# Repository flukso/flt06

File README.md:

# flt06
PCB for testing the Fluksometer

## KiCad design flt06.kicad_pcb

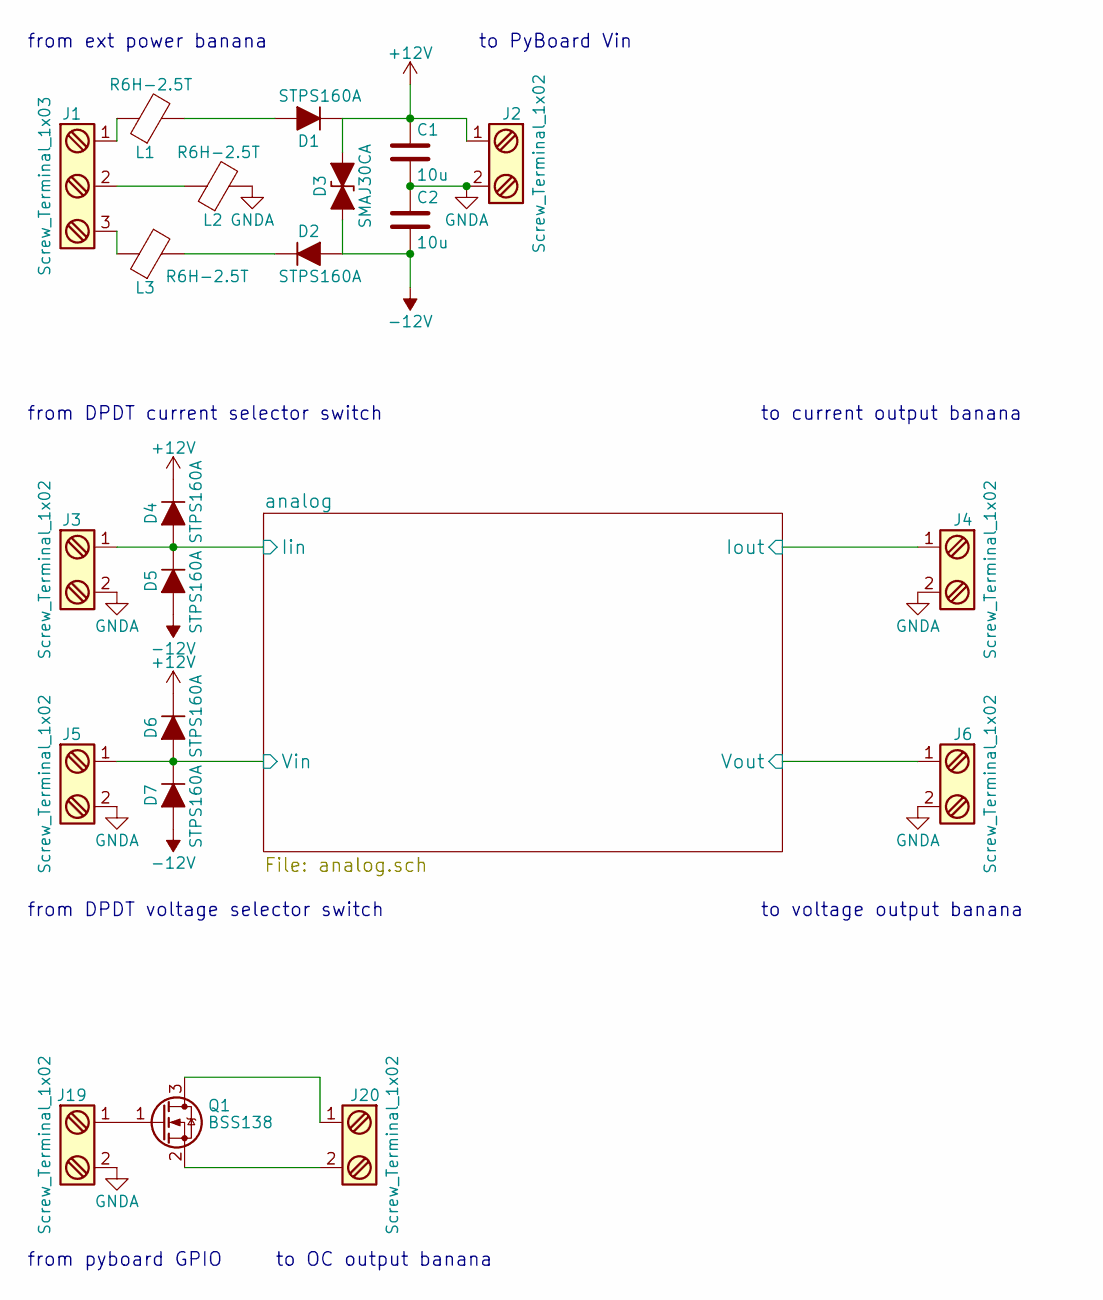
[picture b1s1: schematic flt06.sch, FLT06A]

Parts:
C1, C2: 10u; C_1210
D1, D2, D4, D5, D6, D7: STPS160A; D_SMA
D3: SMAJ30CA; D_SMA
J1: Screw_Terminal_1x03; TerminalBlock_Pheonix_PT-3.5mm_3pol
J2, J3, J4, J5, J6, J19, J20: Screw_Terminal_1x02; TerminalBlock_Pheonix_PT-3.5mm_2pol
L1, L2, L3: R6H-2.5T; R_Axial_DIN0617_L17.0mm_D6.0mm_P5.08mm_Vertical
Q1: BSS138; SOT-23

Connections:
+12V: C1.1, D1.1 (K), D3.2 (A2), D4.1 (K), D6.1 (K), J2.1; also elsewhere on the board
-12V: C2.2, D2.2 (A), D3.1 (A1), D5.2 (A), D7.2 (A); also elsewhere on the board
/analog/Iin: D4.2 (A), D5.1 (K), J3.1; also elsewhere on the board
/analog/Iout: J4.1; also elsewhere on the board
/analog/Vin: D6.2 (A), D7.1 (K), J5.1; also elsewhere on the board
/analog/Vout: J6.1; also elsewhere on the board
GNDA: C1.2, C2.1, J2.2, J3.2, J4.2, J5.2, J6.2, J19.2, L2.2; also elsewhere on the board
unnamed: D1.2 (A), L1.2
unnamed: D2.1 (K), L3.2
unnamed: J1.1, L1.1
unnamed: J1.2, L2.1
unnamed: J1.3, L3.1
unnamed: J19.1, Q1.1 (G)
unnamed: J20.1, Q1.3 (D)
unnamed: J20.2, Q1.2 (S)

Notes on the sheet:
to PyBoard Vin
from ext power banana
from DPDT current selector switch
from DPDT voltage selector switch
to current output banana
to voltage output banana
from pyboard GPIO
to OC output banana

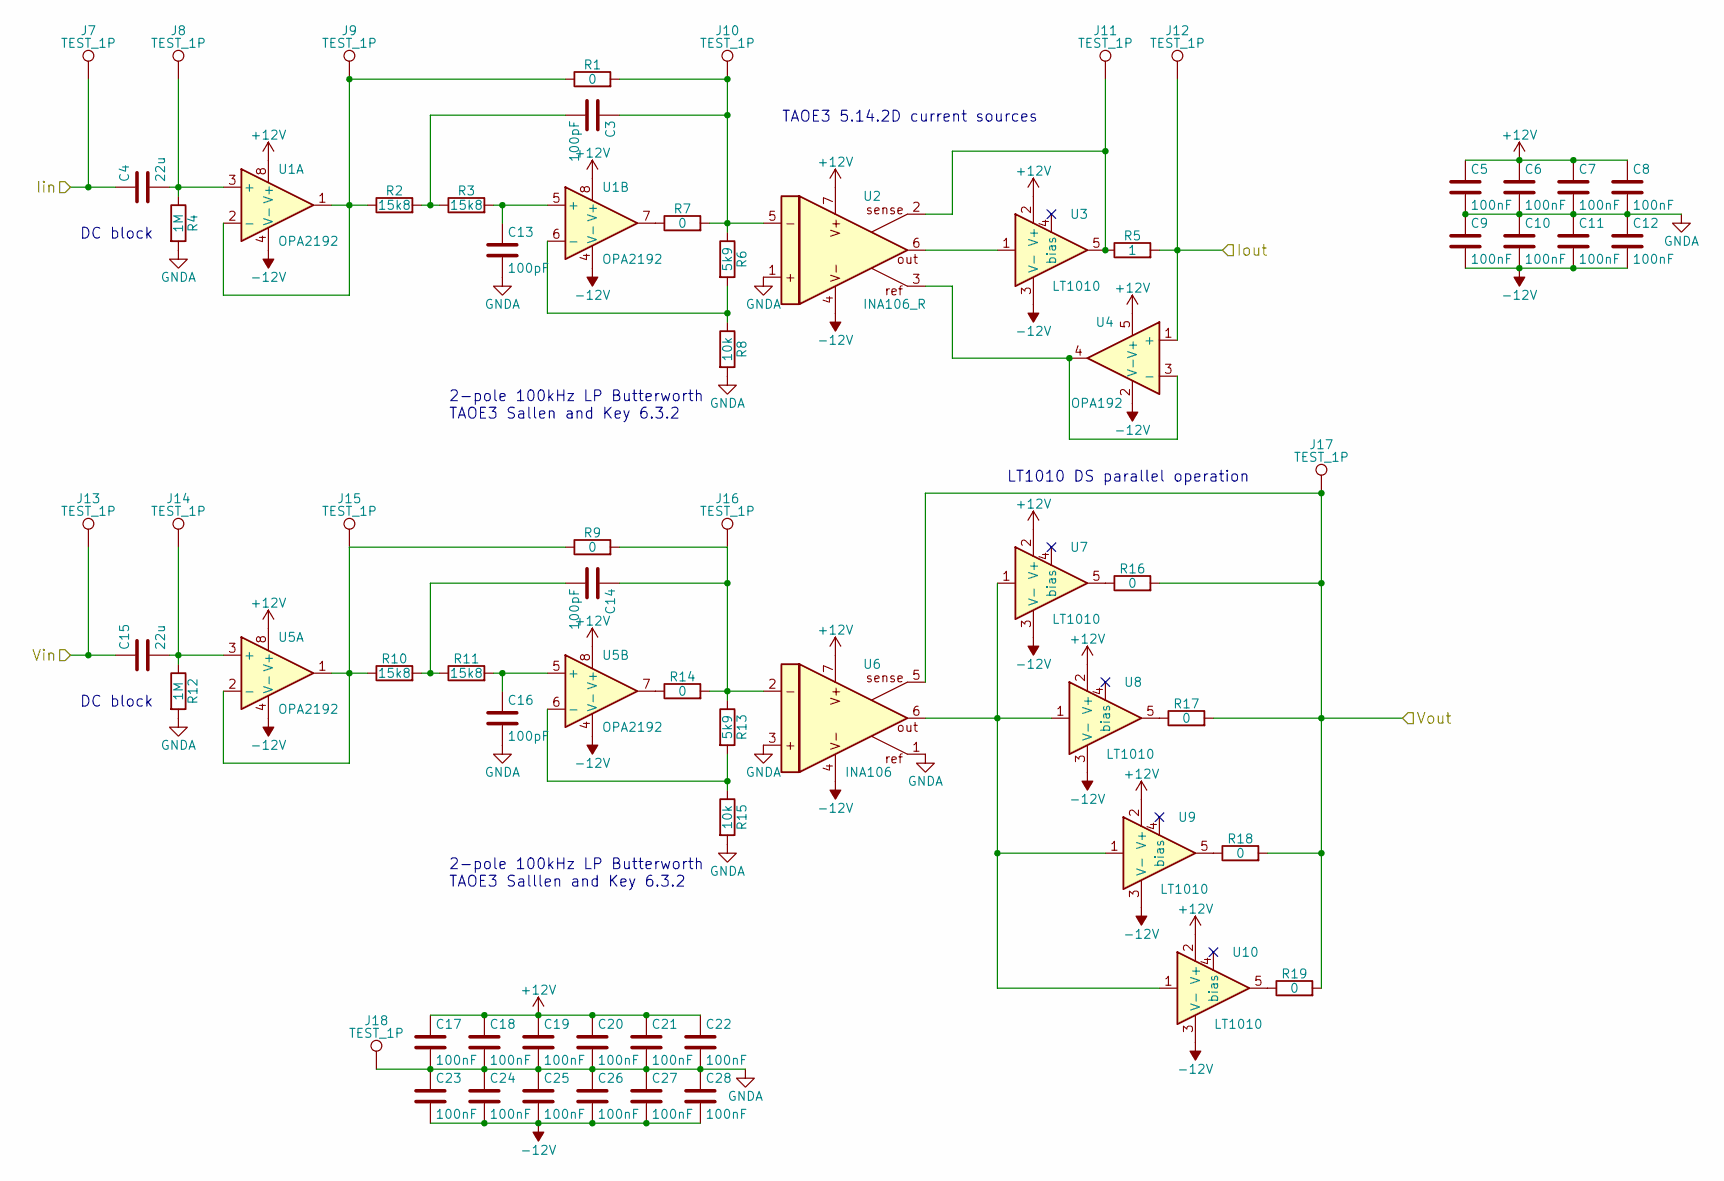
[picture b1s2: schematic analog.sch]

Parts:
C3, C13, C14, C16: 100pF; C_0603
C4, C15: 22u; C_1210
C5, C6, C7, C8, C9, C10, C11, C12, C17, C18, C19, C20, C21, C22, C23, C24, C25, C26, C27, C28: 100nF; C_0603
J7, J8, J9, J10, J11, J12, J13, J14, J15, J16, J17, J18: TEST_1P; Pin_Header_Straight_1x01_Pitch2.54mm
R1, R7, R9, R14: 0; R_0603
R2, R3, R10, R11: 15k8; R_0603
R4, R12: 1M; R_0603
R5: 1; R_1206
R6, R13: 5k9; R_0603
R8, R15: 10k; R_0603
R16, R17, R18, R19: 0; R_1206
U1, U5: OPA2192; TSSOP-8_3x3mm_Pitch0.65mm
U2: INA106_R; SOIC-8_3.9x4.9mm_Pitch1.27mm
U3, U7, U8, U9, U10: LT1010; TO-220-5_Pentawatt_Multiwatt-5_Vertical_StaggeredType1
U4: OPA192; SOT-23-5
U6: INA106; SOIC-8_3.9x4.9mm_Pitch1.27mm

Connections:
+12V: C5.1, C6.1, C7.1, C8.1, C17.1, C18.1, C19.1, C20.1, C21.1, C22.1, U1.8 (V+), U2.7, U3.2 (V+), U4.5 (V+), U5.8 (V+), U6.7, U7.2 (V+), U8.2 (V+), U9.2 (V+), U10.2 (V+); also elsewhere on the board
-12V: C9.2, C10.2, C11.2, C12.2, C23.2, C24.2, C25.2, C26.2, C27.2, C28.2, U1.4 (V-), U2.4, U3.3 (V-), U4.2 (V-), U5.4 (V-), U6.4, U7.3 (V-), U8.3 (V-), U9.3 (V-), U10.3 (V-); also elsewhere on the board
/analog/Iin: C4.1, J7.1; also elsewhere on the board
/analog/Iout: J12.1, R5.2, U4.1 (+); also elsewhere on the board
/analog/Vin: C15.1, J13.1; also elsewhere on the board
/analog/Vout: J17.1, R16.2, R17.2, R18.2, R19.2, U6.5; also elsewhere on the board
GNDA: C5.2, C6.2, C7.2, C8.2, C9.1, C10.1, C11.1, C12.1, C13.2, C16.2, C17.2, C18.2, C19.2, C20.2, C21.2, C22.2, C23.1, C24.1, C25.1, C26.1, C27.1, C28.1, J18.1, R4.2, R8.2, R12.2, R15.2, U2.1, U6.1, U6.3; also elsewhere on the board
unnamed: C3.1, J10.1, R1.2, R6.1, R7.2, U2.5
unnamed: C3.2, R2.2, R3.1
unnamed: C4.2, J8.1, R4.1, U1.3 (+)
unnamed: C13.1, R3.2, U1.5 (+)
unnamed: C14.1, J16.1, R9.2, R13.1, R14.2, U6.2
unnamed: C14.2, R10.2, R11.1
unnamed: C15.2, J14.1, R12.1, U5.3 (+)
unnamed: C16.1, R11.2, U5.5 (+)
unnamed: J9.1, R1.1, R2.1, U1.1, U1.2 (-)
unnamed: J11.1, R5.1, U2.2, U3.5
unnamed: J15.1, R9.1, R10.1, U5.1, U5.2 (-)
unnamed: R6.2, R8.1, U1.6 (-)
unnamed: R7.1, U1.7
unnamed: R13.2, R15.1, U5.6 (-)
unnamed: R14.1, U5.7
unnamed: R16.1, U7.5
unnamed: R17.1, U8.5
unnamed: R18.1, U9.5
unnamed: R19.1, U10.5
unnamed: U2.3, U4.3 (-), U4.4
unnamed: U2.6, U3.1
unnamed: U6.6, U7.1, U8.1, U9.1, U10.1

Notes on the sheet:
2-pole 100kHz LP Butterworth TAOE3 Sallen and Key 6.3.2
2-pole 100kHz LP Butterworth TAOE3 Salllen and Key 6.3.2
TAOE3 5.14.2D current sources
LT1010 DS parallel operation
DC block

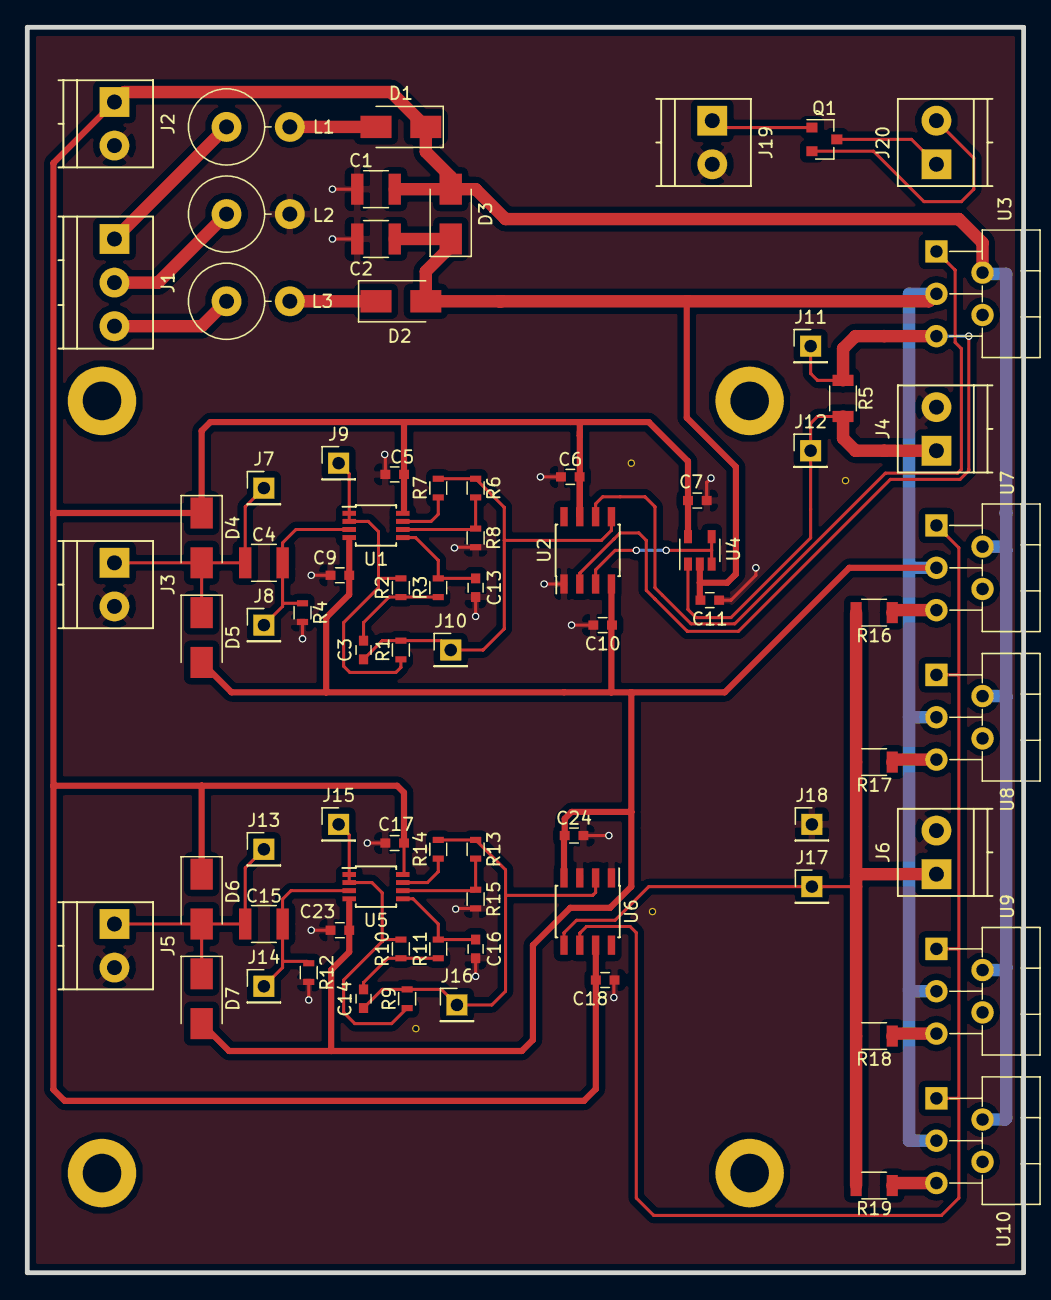
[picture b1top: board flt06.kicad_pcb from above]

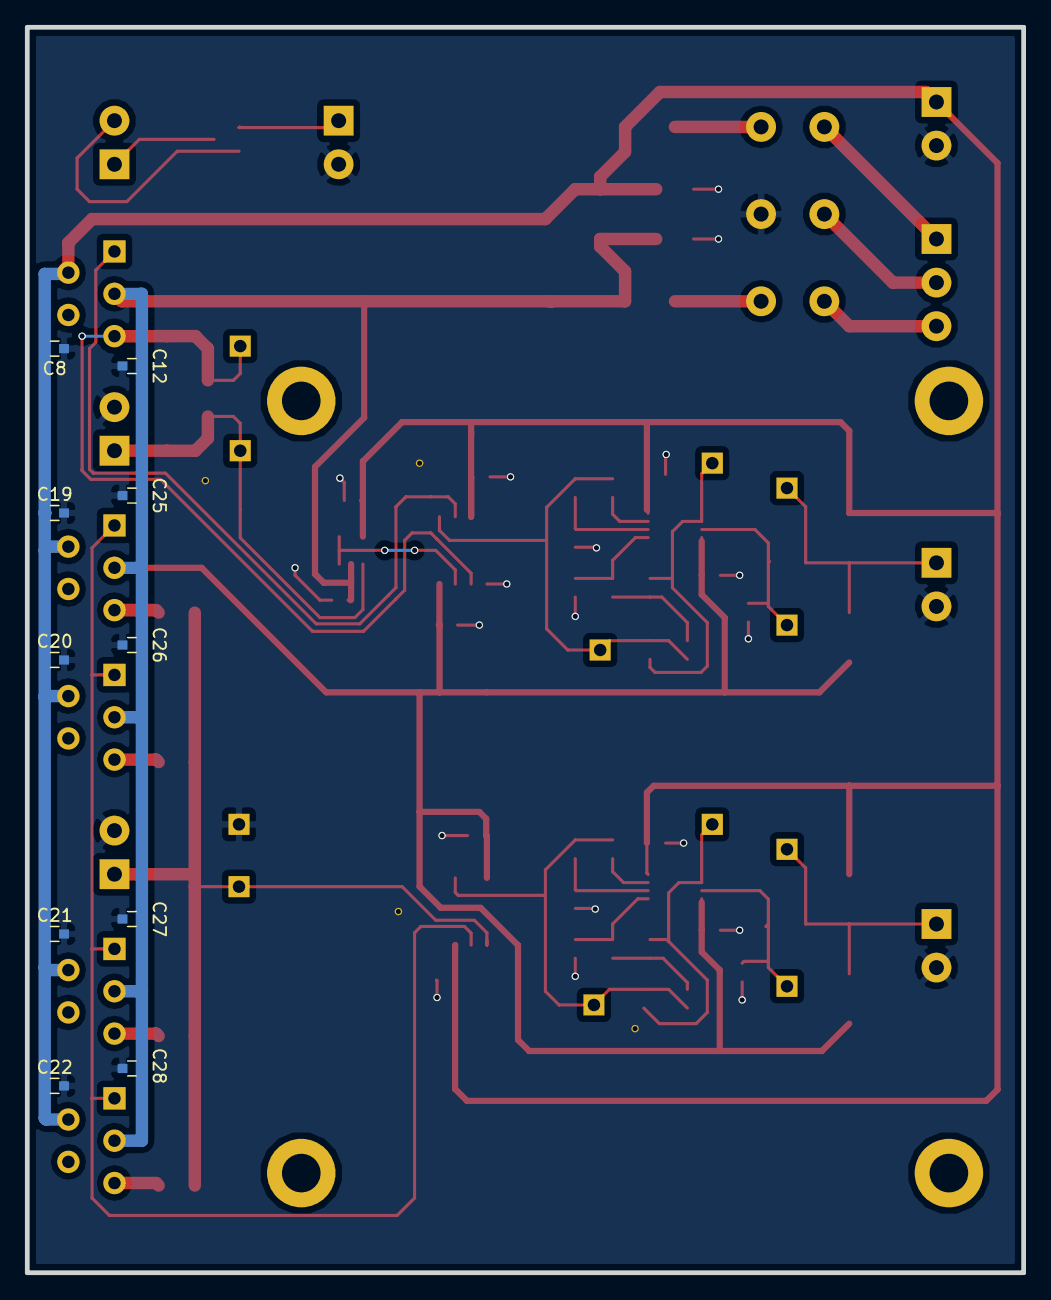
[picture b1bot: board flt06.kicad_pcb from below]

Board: 2 copper layers, 80.0 x 100.0 mm, 90 parts (10 on the bottom side), 37 nets.

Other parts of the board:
flukso: flukso; logo_mask
fluksobot: fluksobot; logo_bot_mask

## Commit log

2017-08-09 [sch] initial commit
2017-08-10 [sch] use an off-the-shelf pyboard to handle the digital part
2017-09-12 [pcb] layout rev1
2017-09-12 [cam] move rev1 cam files
